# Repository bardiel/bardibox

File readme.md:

# Bardibox

Midibox based MIDI controller.

All hardware is based on MidiBox:
http://ucapps.de

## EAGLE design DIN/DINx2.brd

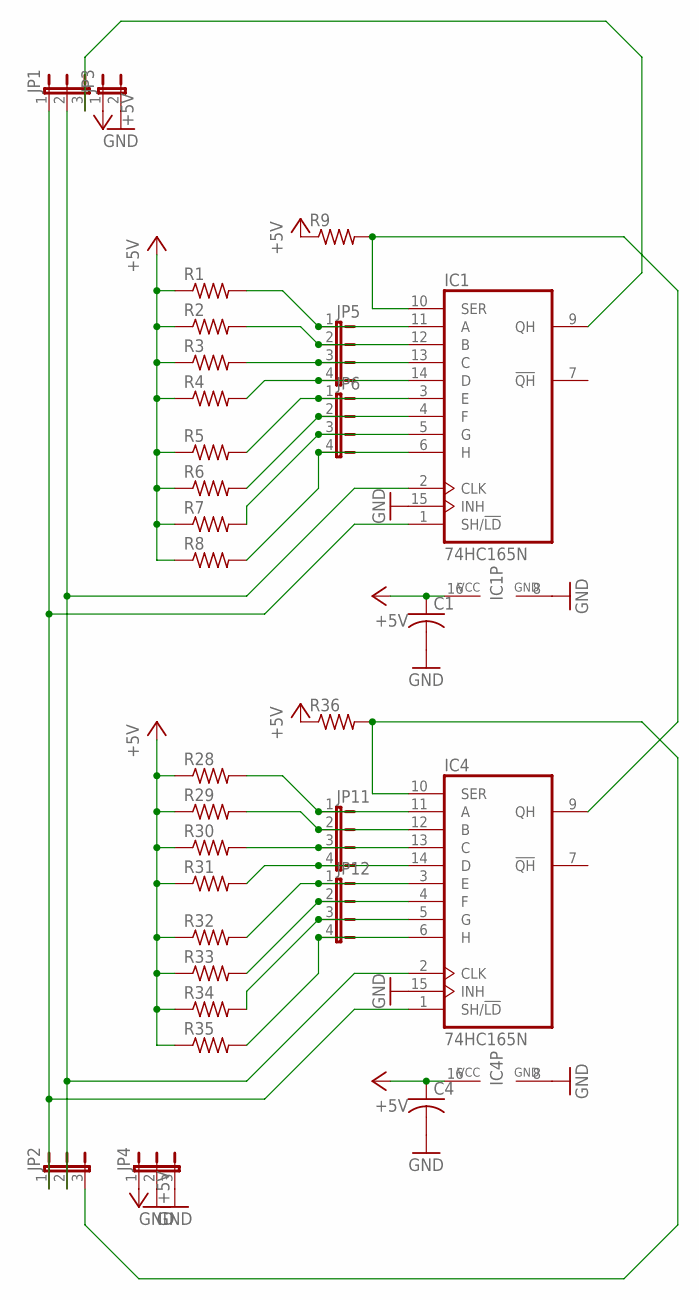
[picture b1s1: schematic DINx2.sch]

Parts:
C1, C4: C-US025-025X050; C025-025X050
IC1, IC4: 74HC165N; DIL16
JP1, JP2, JP4: JP2E; JP2
JP3: JP1E; JP1
JP5, JP6, JP11, JP12: JP4E; JP4
R1, R2, R3, R4, R5, R6, R7, R8, R9, R28, R29, R30, R31, R32, R33, R34, R35, R36: R-US_0207/2V; 0207/2V

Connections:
+5V: C1.1, C4.1, IC1.16 (VCC), IC4.16 (VCC), JP3.1, JP4.1, R1.1, R2.1, R3.1, R4.1, R5.1, R6.1, R7.1, R8.1, R9.1, R28.1, R29.1, R30.1, R31.1, R32.1, R33.1, R34.1, R35.1, R36.1
GND: C1.2, C4.2, IC1.8 (GND), IC1.15 (INH), IC4.8 (GND), IC4.15 (INH), JP3.2, JP4.2, JP4.3
unnamed: IC1.11 (A), JP5.1, R1.2
unnamed: IC1.12 (B), JP5.2, R2.2
unnamed: IC1.3 (E), JP6.1, R5.2
unnamed: IC1.13 (C), JP5.3, R3.2
unnamed: IC1.14 (D), JP5.4, R4.2
unnamed: IC1.4 (F), JP6.2, R6.2
unnamed: IC1.5 (G), JP6.3, R7.2
unnamed: IC1.6 (H), JP6.4, R8.2
unnamed: IC1.9 (QH), JP1.3
unnamed: IC1.1 (SH/!LD), IC4.1 (SH/!LD), JP1.1, JP2.1
unnamed: IC1.2 (CLK), IC4.2 (CLK), JP1.2, JP2.2
unnamed: IC4.11 (A), JP11.1, R28.2
unnamed: IC4.13 (C), JP11.3, R30.2
unnamed: IC4.14 (D), JP11.4, R31.2
unnamed: IC4.12 (B), JP11.2, R29.2
unnamed: IC4.3 (E), JP12.1, R32.2
unnamed: IC4.5 (G), JP12.3, R34.2
unnamed: IC4.6 (H), JP12.4, R35.2
unnamed: IC4.4 (F), JP12.2, R33.2
unnamed: IC1.10 (SER), IC4.9 (QH), R9.2
unnamed: IC4.10 (SER), JP2.3, R36.2

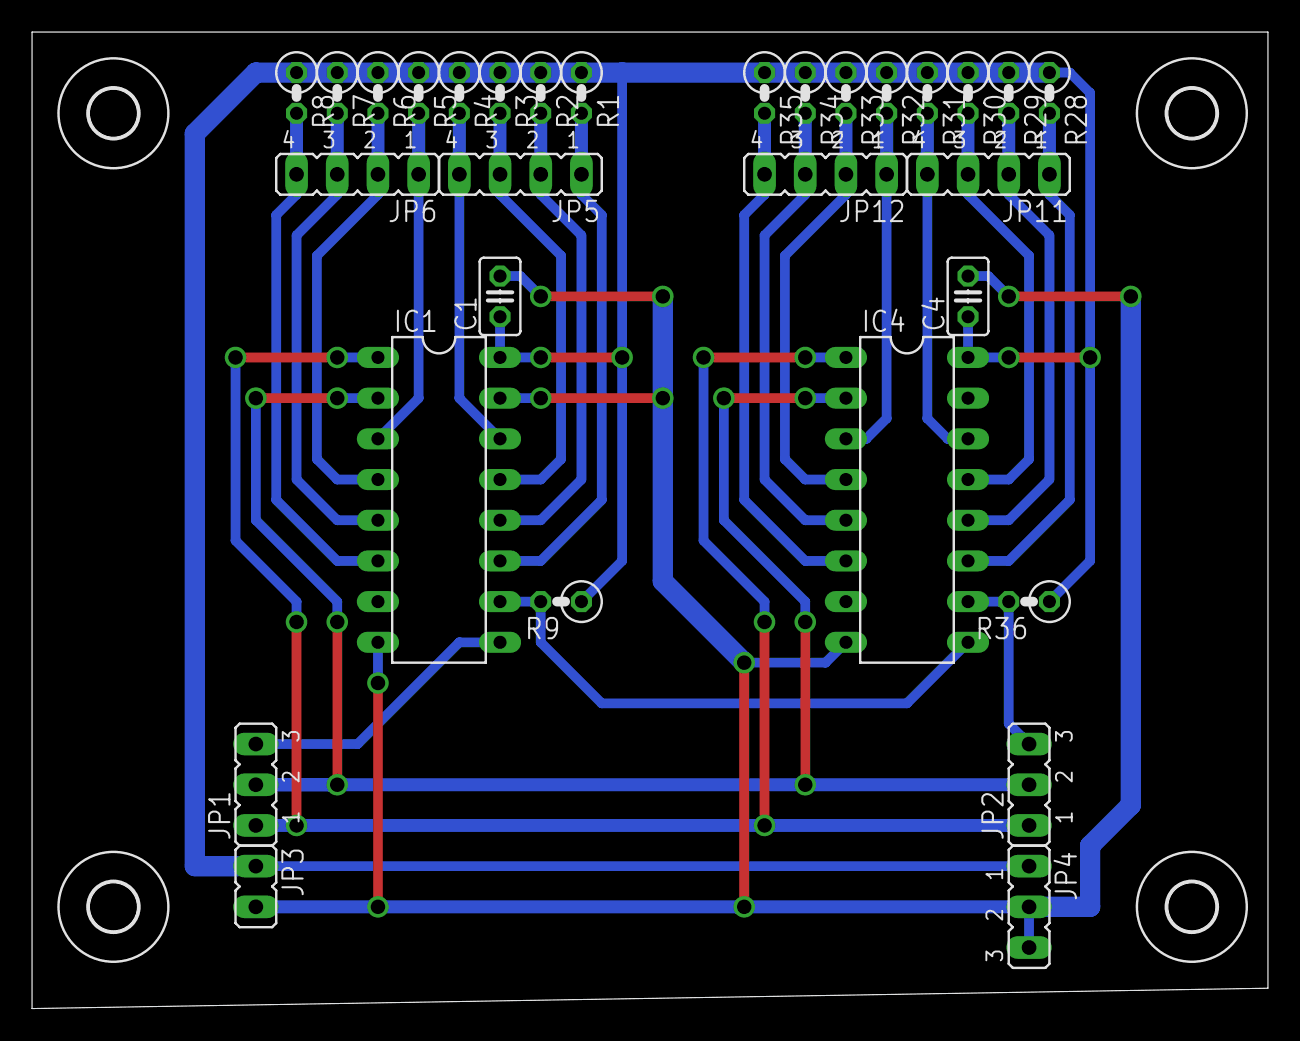
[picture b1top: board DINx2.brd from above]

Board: 2 copper layers, 77.1 x 61.0 mm, 34 parts (0 on the bottom side), 23 nets.

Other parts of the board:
U$1, U$2, U$3, U$4: 3,0

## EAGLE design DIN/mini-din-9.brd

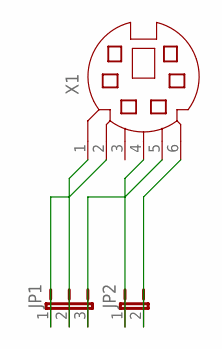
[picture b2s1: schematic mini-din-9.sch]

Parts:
JP1: JP2E; JP2
JP2: JP1E; JP1
X1: MD06SS; MDIN06SS

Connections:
unnamed: JP1.1, X1.2
unnamed: JP1.2, X1.1
unnamed: JP1.3, X1.5
unnamed: JP2.1, X1.4
unnamed: JP2.2, X1.6

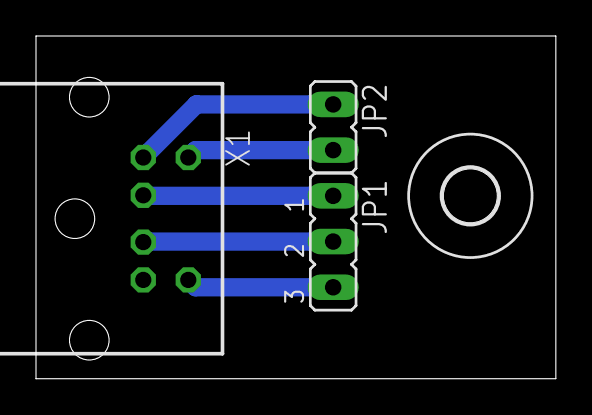
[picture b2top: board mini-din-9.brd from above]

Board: 2 copper layers, 28.9 x 19.0 mm, 4 parts (0 on the bottom side), 5 nets.

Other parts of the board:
U$1: 3,0

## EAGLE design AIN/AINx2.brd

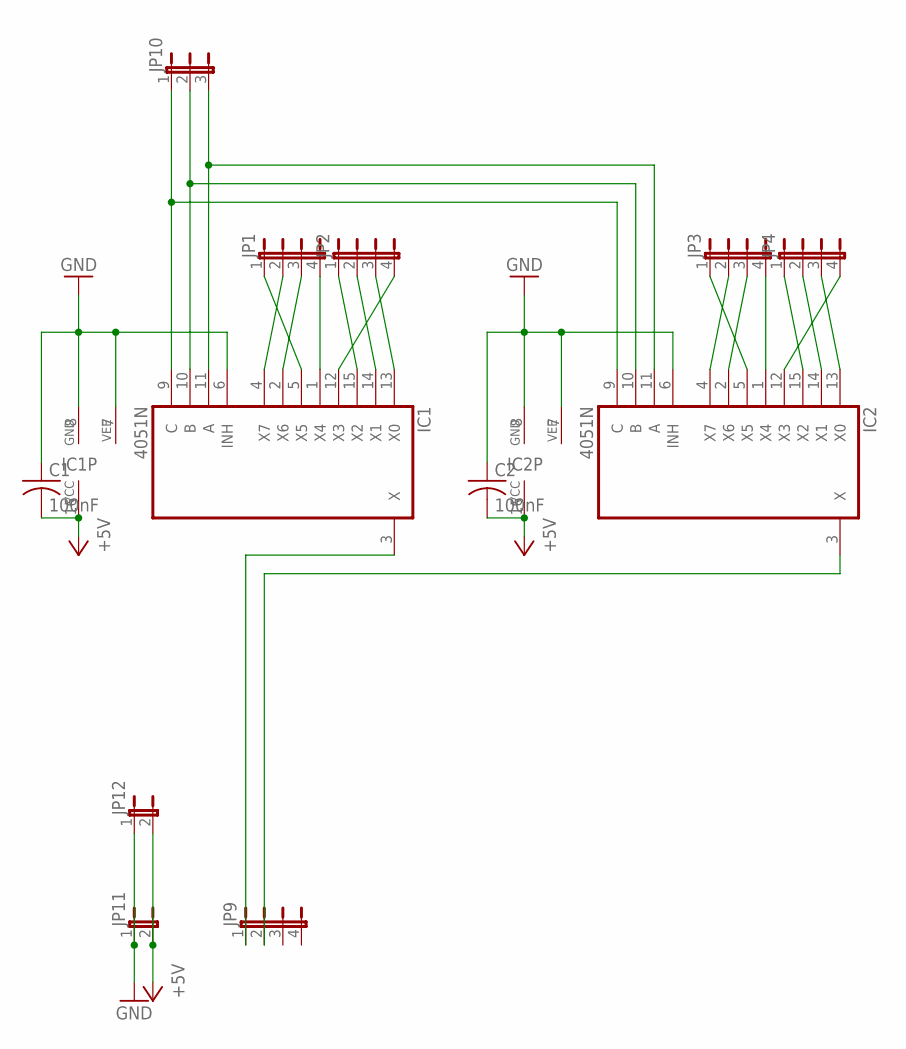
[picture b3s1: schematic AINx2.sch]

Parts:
C1, C2: 100nF; C025-025X050
IC1, IC2: 4051N; DIL16
JP1, JP2, JP3, JP4, JP9: JP4E; JP4
JP10: JP2E; JP2
JP11, JP12: JP1E; JP1

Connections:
+5V: C1.2, C2.2, IC1.16 (VCC), IC2.16 (VCC), JP11.2, JP12.2
GND: C1.1, C2.1, IC1.6 (INH), IC1.7 (VEE), IC1.8 (GND), IC2.6 (INH), IC2.7 (VEE), IC2.8 (GND), JP11.1, JP12.1
unnamed: IC1.1 (X4), JP1.4
unnamed: IC1.2 (X6), JP1.3
unnamed: IC1.9 (C), IC2.9 (C), JP10.1
unnamed: IC1.10 (B), IC2.10 (B), JP10.2
unnamed: IC1.11 (A), IC2.11 (A), JP10.3
unnamed: IC1.4 (X7), JP1.2
unnamed: IC1.5 (X5), JP1.1
unnamed: IC1.15 (X2), JP2.1
unnamed: IC1.14 (X1), JP2.2
unnamed: IC1.13 (X0), JP2.3
unnamed: IC1.12 (X3), JP2.4
unnamed: IC2.1 (X4), JP3.4
unnamed: IC2.2 (X6), JP3.3
unnamed: IC2.4 (X7), JP3.2
unnamed: IC2.5 (X5), JP3.1
unnamed: IC2.15 (X2), JP4.1
unnamed: IC2.14 (X1), JP4.2
unnamed: IC2.13 (X0), JP4.3
unnamed: IC2.12 (X3), JP4.4
unnamed: IC1.3 (X), JP9.1
unnamed: IC2.3 (X), JP9.2

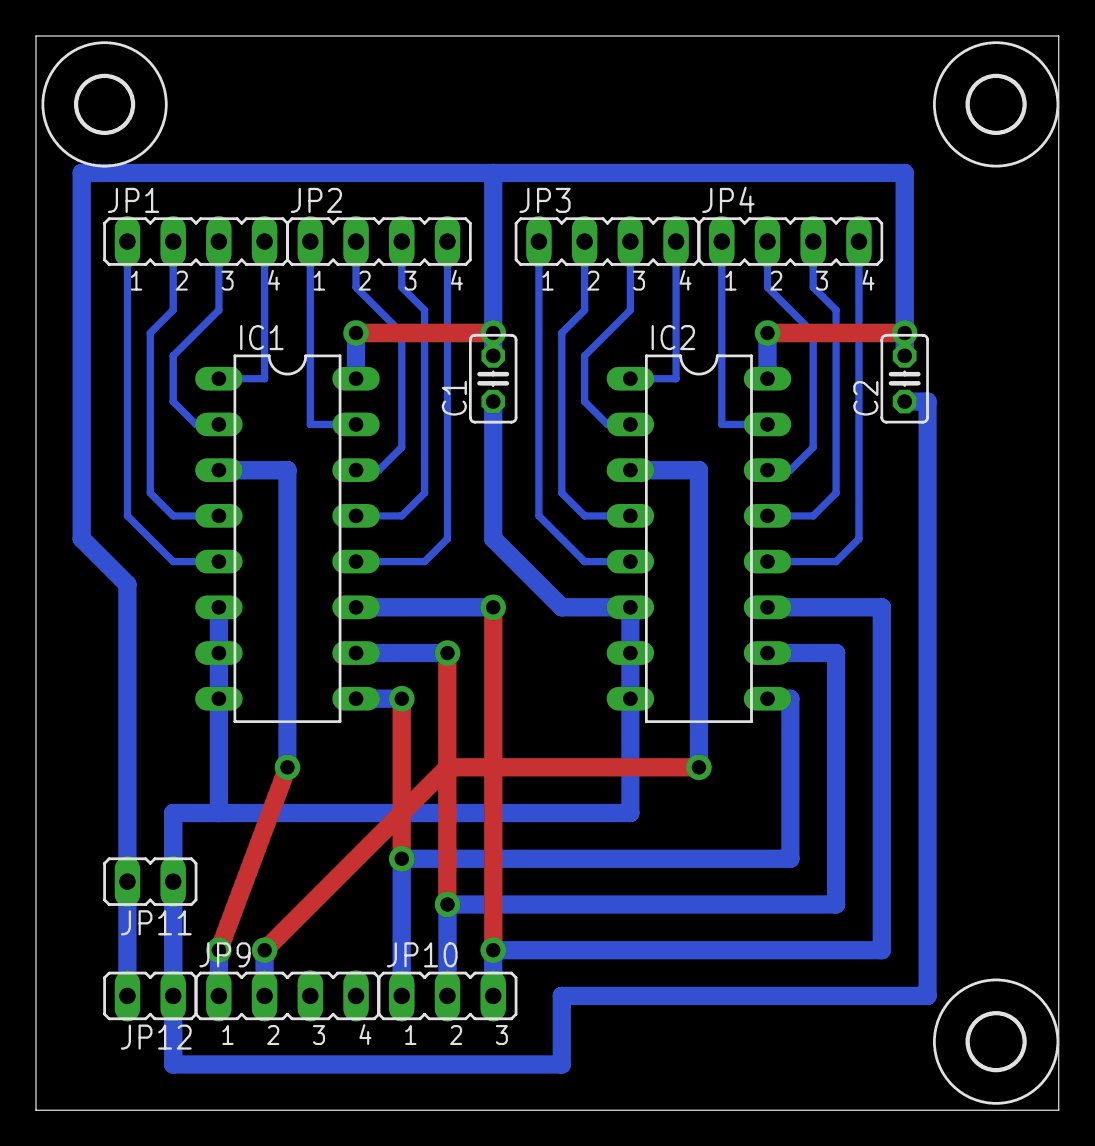
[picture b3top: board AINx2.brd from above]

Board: 2 copper layers, 56.8 x 59.7 mm, 15 parts (0 on the bottom side), 23 nets.

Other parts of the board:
U$1, U$2, U$3: 3,0

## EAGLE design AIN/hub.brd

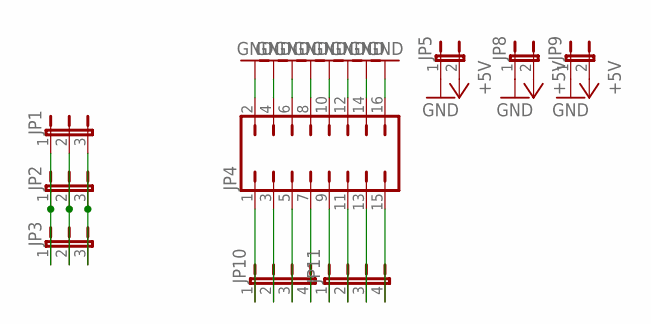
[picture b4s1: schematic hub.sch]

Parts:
JP1, JP2, JP3: JP2E; JP2
JP4: JP8Q
JP5, JP8, JP9: JP1E; JP1
JP10, JP11: JP4E; JP4

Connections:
+5V: JP5.2, JP8.2, JP9.2
GND: JP4.2, JP4.4, JP4.6, JP4.8, JP4.10, JP4.12, JP4.14, JP4.16, JP5.1, JP8.1, JP9.1
unnamed: JP1.1, JP2.1, JP3.1
unnamed: JP1.2, JP2.2, JP3.2
unnamed: JP1.3, JP2.3, JP3.3
unnamed: JP4.1, JP10.1
unnamed: JP4.3, JP10.2
unnamed: JP4.5, JP10.3
unnamed: JP4.7, JP10.4
unnamed: JP4.9, JP11.1
unnamed: JP4.11, JP11.2
unnamed: JP4.13, JP11.3
unnamed: JP4.15, JP11.4

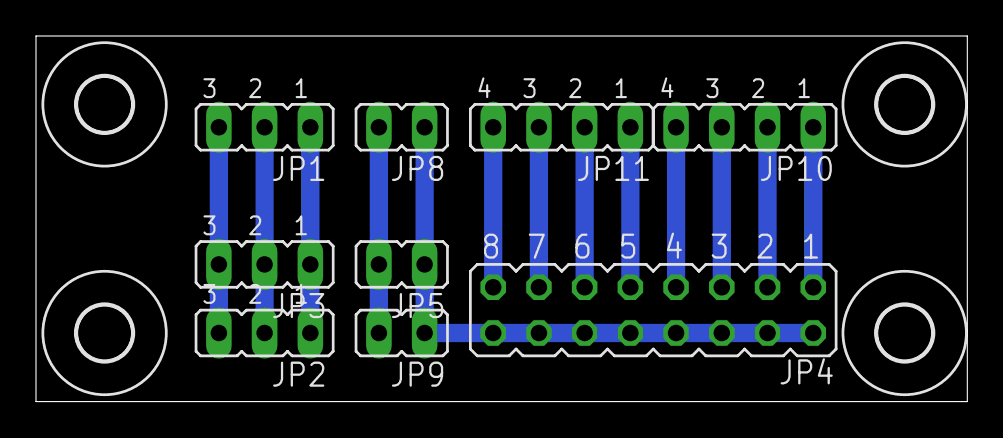
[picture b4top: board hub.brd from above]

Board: 2 copper layers, 51.7 x 20.3 mm, 13 parts (0 on the bottom side), 13 nets.

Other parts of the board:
U$1, U$2, U$3, U$4: 3,0

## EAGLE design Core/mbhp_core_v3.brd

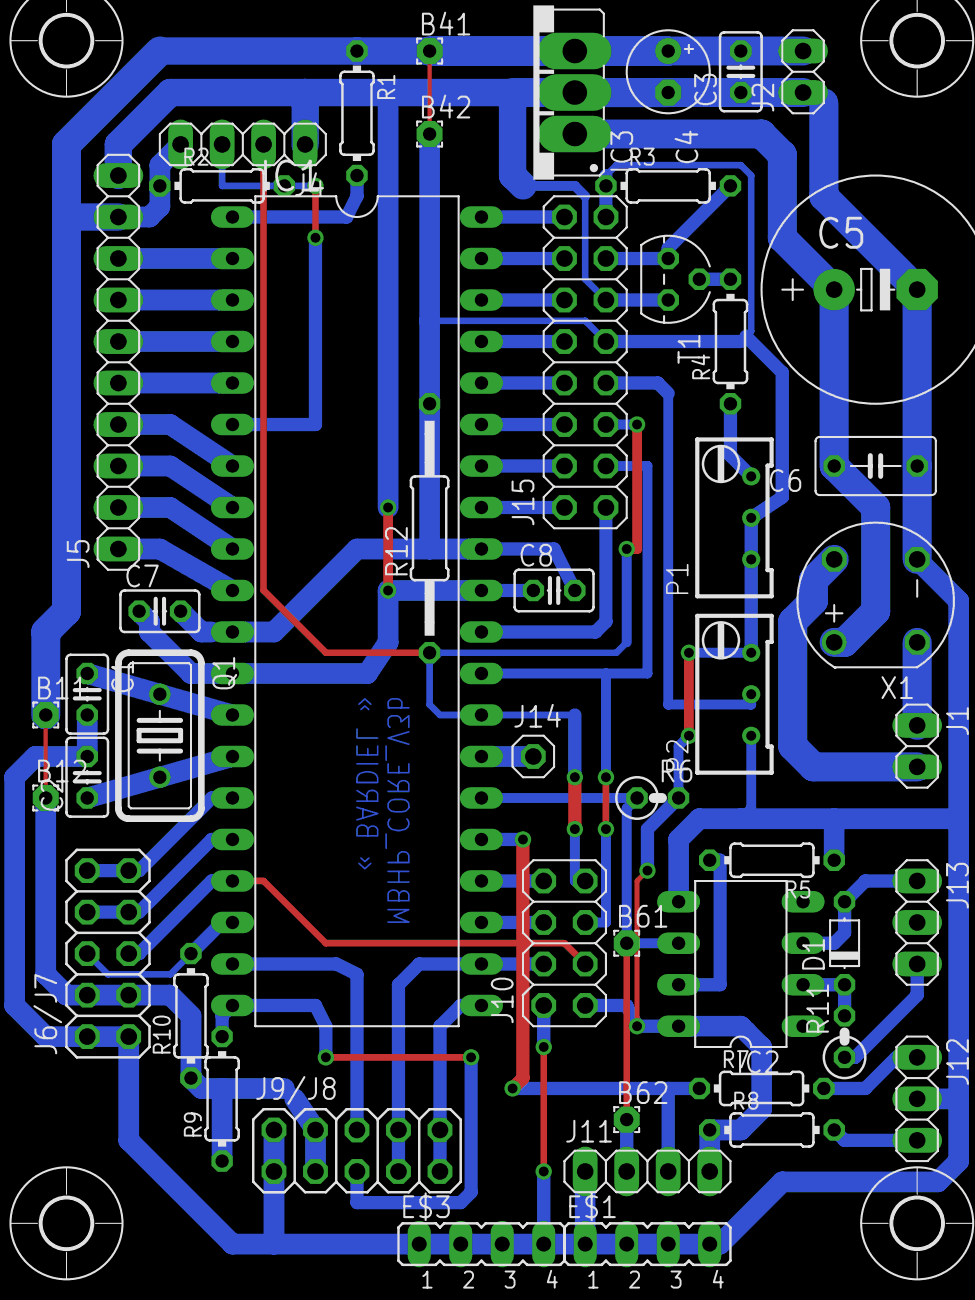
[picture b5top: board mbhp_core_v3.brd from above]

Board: 2 copper layers, 53 parts (0 on the bottom side), 51 nets.

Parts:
B11, B12, B41, B42, B61, B62: 1,6/0,8
C1, C2: 33pF; C025-025X050
C3, C7, C8: 100nF; C025-025X050
C4: 10uF; E2,5-5
C5: 2200uF; E5-13
C6: 330nF; C050-035X075
D1: 1N4148; D-5
E$1, E$3: JP4
E$26, E$27, E$28, E$29: 3,0
IC1: PIC18F452; DIL40
IC2: 6N138; DIL08
IC3: 7805; 78XXS_
J1, J2: 1X02
J4, J11: 1X04
J5: 1X10
J6/J7, J9/J8: 2X05
J10: 2X04
J12, J13: 1X03
J14: 1X01
J15: 2X08
P1, P2: 10k; RTRIM64W
Q1: 10-HC18; HC18U-V
R1: 100; 0204/7
R2, R4: 1k; 0204/7
R3, R9, R10: 10k; 0204/7
R5: 5.6k; 0204/7
R6: 1.2k; 0207/2V
R7, R8: 220; 0204/7
R11: 220; 0207/2V
R12: 1k; 0207/15
T1: BC337; TO92
X1: RB1A

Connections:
P2: J15.7, P2.2
S$1: C1.1, IC1.13, Q1.1
S$2: C2.1, IC1.14, Q1.2
S$3: R4.2, T1.2
S$4: IC1.40, J15.16
S$5: P1.3, R4.1
S$6: IC1.39, J15.14
S$7: IC1.1, R1.2
S$9: IC1.28, J10.7, J15.5, R12.1
S$10: IC1.22, J9/J8.7, J9/J8.8, J10.4
S$11: IC1.6, J4.3, R2.2
S$12: IC1.15, J6/J7.9, J6/J7.10
S$13: IC1.16, J6/J7.7, J6/J7.8
S$14: IC1.10, J5.1
S$15: IC1.9, J5.2
S$16: IC1.8, J5.3
S$17: IC1.7, J5.4
S$18: IC1.5, J5.5
S$19: IC1.4, J5.6
S$20: IC1.3, J5.7
S$21: IC1.2, J5.8
S$23: IC1.17, J6/J7.5, J10.3
S$24: IC1.18, J6/J7.6, R10.2
S$25: IC1.20, J9/J8.5, R9.2
S$26: IC1.19, J9/J8.6
S$27: IC1.33, J15.2
S$28: IC1.34, J15.4
S$29: IC1.35, J15.6
S$30: IC1.36, J15.8
S$31: IC1.37, J15.10
S$32: IC1.38, J15.12
S$35: IC1.30, J15.1
S$36: IC1.29, J10.5, J15.3
S$39: J15.13, R3.2, T1.3
S$42: B61.1, B62.1, IC1.26, IC2.6, J11.2, R6.1
S$43: IC2.7, R5.2
S$44: D1.A, IC2.3, J13.1
S$45: D1.C, IC2.2, R11.2
S$46: C5.+, C6.2, IC3.IN, X1.+
S$47: J12.1, R7.2
S$48: J12.3, R8.2
S$49: IC1.23, J10.6
S$50: IC1.24, J10.8
S$51: IC1.25, J11.3, R7.1
S$52: J1.1, X1.AC2
S$53: J1.2, X1.AC1
S$54: J13.3, R11.1
S$55: IC1.27, J14.1
S$56: IC1.21, J9/J8.9, J9/J8.10
VDD: B11.1, B12.1, B41.1, B42.1, C3.2, C4.+, C7.2, C8.2, IC1.11, IC1.32, IC2.8, IC3.OUT, J2.2, J4.4, J5.9, J6/J7.3, J6/J7.4, J9/J8.3, J9/J8.4, J10.1, J11.4, J15.9, J15.15, P1.1, P1.2, P2.3, R1.1, R2.1, R3.1, R6.2, R8.1, R9.1, R10.1, R12.2
VSS: C1.2, C2.2, C3.1, C4.-, C5.-, C6.1, C7.1, C8.1, IC1.12, IC1.31, IC2.5, IC3.GND, J2.1, J4.1, J5.10, J6/J7.1, J6/J7.2, J9/J8.1, J9/J8.2, J10.2, J11.1, J12.2, J15.11, P2.1, R5.1, T1.1, X1.-

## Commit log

2014-03-08 MBDIN-MBCORE connection with minidin-9 connector
2015-12-23 DOUTx3 Schematics
2015-12-23 starting DOUTx3 brd
